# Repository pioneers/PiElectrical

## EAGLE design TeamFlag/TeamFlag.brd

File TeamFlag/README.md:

#Team Flag

The Flag for the Robot, display California Gold or Yale Blue

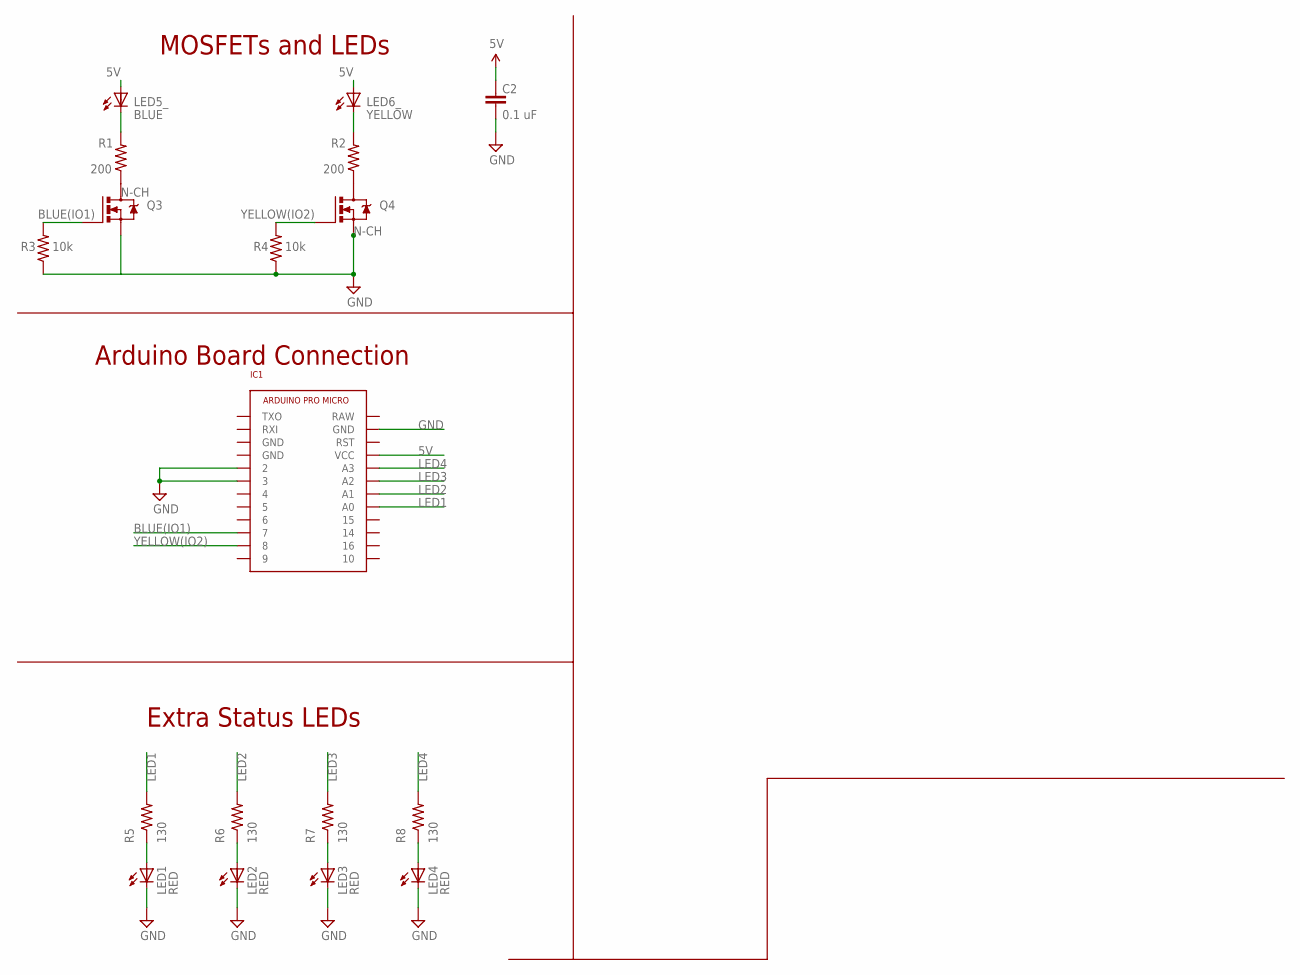
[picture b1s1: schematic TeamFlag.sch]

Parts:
C2: 0.1 uF; 0603-CAP
IC1: ARDUINO_PRO_MICROSMD; ARDUINO_PRO_MICRO_SM
LED1, LED2, LED3, LED4: RED; LED-0805
LED5_: BLUE; LED5MM-NOFLAT
LED6_: YELLOW; LED5MM-NOFLAT
Q3, Q4: N-CH; SOT23-3
R1, R2: 200; R0603
R3, R4: 10k; R0603
R5, R6, R7, R8: 130; R0603

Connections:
5V: C2.1, IC1.VCC, LED5_.A, LED6_.A
BLUE(IO1): IC1.7, Q3.1 (G), R3.2
BSOURCE: Q3.3 (D), R1.1
GND: C2.2, IC1.2, IC1.3, IC1.GND@2 (GND), LED1.C, LED2.C, LED3.C, LED4.C, Q3.2 (S), Q4.2 (S), R3.1, R4.1
LED1: IC1.A0, R5.2
LED1R: LED1.A, R5.1
LED2: IC1.A1, R6.2
LED2R: LED2.A, R6.1
LED3: IC1.A2, R7.2
LED3R: LED3.A, R7.1
LED4: IC1.A3, R8.2
LED4R: LED4.A, R8.1
unnamed: LED5_.K (C), R1.2
unnamed: LED6_.K (C), R2.2
YELLOW(IO2): IC1.8, Q4.1 (G), R4.2
YSOURCE: Q4.3 (D), R2.1

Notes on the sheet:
MOSFETs and LEDs
Extra Status LEDs
Arduino Board Connection

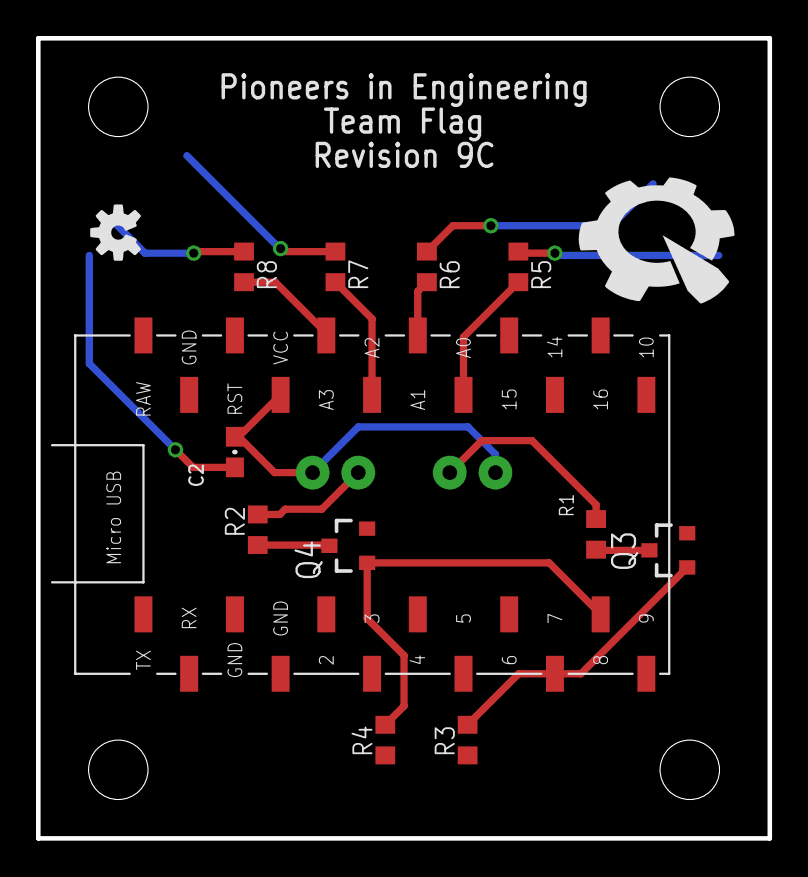
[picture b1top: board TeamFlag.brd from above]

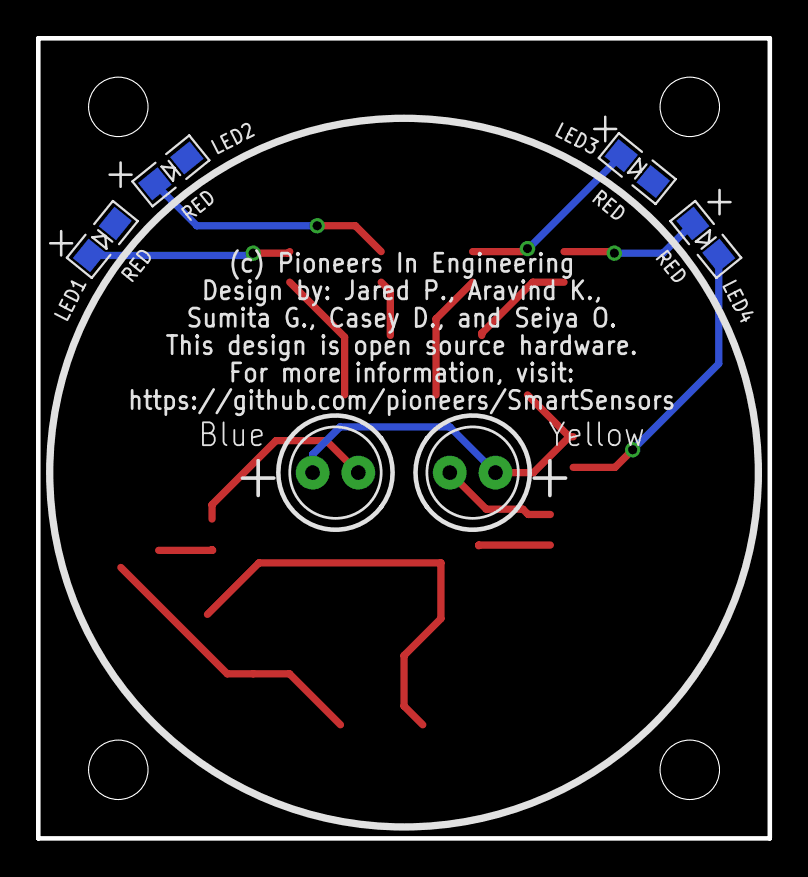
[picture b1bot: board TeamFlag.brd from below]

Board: 2 copper layers, 40.6 x 44.5 mm, 24 parts (6 on the bottom side), 16 nets.

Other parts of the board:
U$1: PIE-LOGO-SMALL
U$2: OSHW-LOGO-S
U$11, U$12, U$13, U$14: STAND-OFF

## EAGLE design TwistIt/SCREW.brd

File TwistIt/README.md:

#TwistIt

Screw terminal based potentiometer/line follower/limit switch ultimate board

Named TwistIt for the screw terminal (open to suggestions)

Digital in Pins are all labeled "Arduino" in the pinout diagram

Analog pins are labeled as such

Analog pins can be used as digital, NOT vice versa

[2 Pin](https://www.sparkfun.com/products/8432) [3 pin](https://www.sparkfun.com/products/8433)

##Reed switches

Basically when it is placed in a magnetic field, the switch closes.

There surface mounts and through hole variants, but generally they have the same working range

For more specs, please view the link below:

http://www.digikey.com/product-search/en/switches/magnetic-reed-switches/1114199

It can be bought from Digikey, Sparkfun, Aliexpress, Amazon.

[AliExpress](https://www.aliexpress.com/item/10pcs-KSK-1A-Reed-Switch-2x14mm-Green-Glass-Usually-Open-For-Sensors-100-Original/32424207994.html)

To test it, connect it in series with a resistor and take the input from the point between them.

A sample of a simple code is shown below:

```
int reed = 2;

int LED = 3;

void setup() {

Serial.begin(9600);

pinMode(reed,INPUT);

pinMode(LED,OUTPUT);

}

void loop() {

if(digitalRead(reed)==HIGH){

digitalWrite(LED, HIGH);

}

else digitalWrite(3, LOW);

}
```
where an LED is attached to pin 3.

Please contact Ren Lingfei for more information.

## Yogi Bear Break Out

VNH2SP30 | APM
-------- | ---
5V | Vcc
GND | GND
EN | 14
INA | 16
INB | 10
CS | 8
PMW | 9
- | -
Encoder A | 2
Encoder B | 3
- | -
Red | 4
Yellow | 5
Green  6

[New Motor 1](https://e-smotor.en.alibaba.com/product/60220884310-801307434/37GB_spur_gear_motor_with_encoder.html?spm=a2700.7803228.1998738836.575.wFZGi0)

[New Motor 2](https://jslmotor.en.alibaba.com/product/60311538644-211952029/12v_24v_Pure_Metal_JGB37_3530B_Permanent_Magnet_High_Torque_24_Volt_Dc_Motor.html?spm=a2700.7803228.1998738836.185.6lh84F)

[Hardware Interrupts](https://www.arduino.cc/en/Reference/AttachInterrupt)

Encoder is all digital. A and B Out need to be pulled up and needs to be mapped to interrupt pins

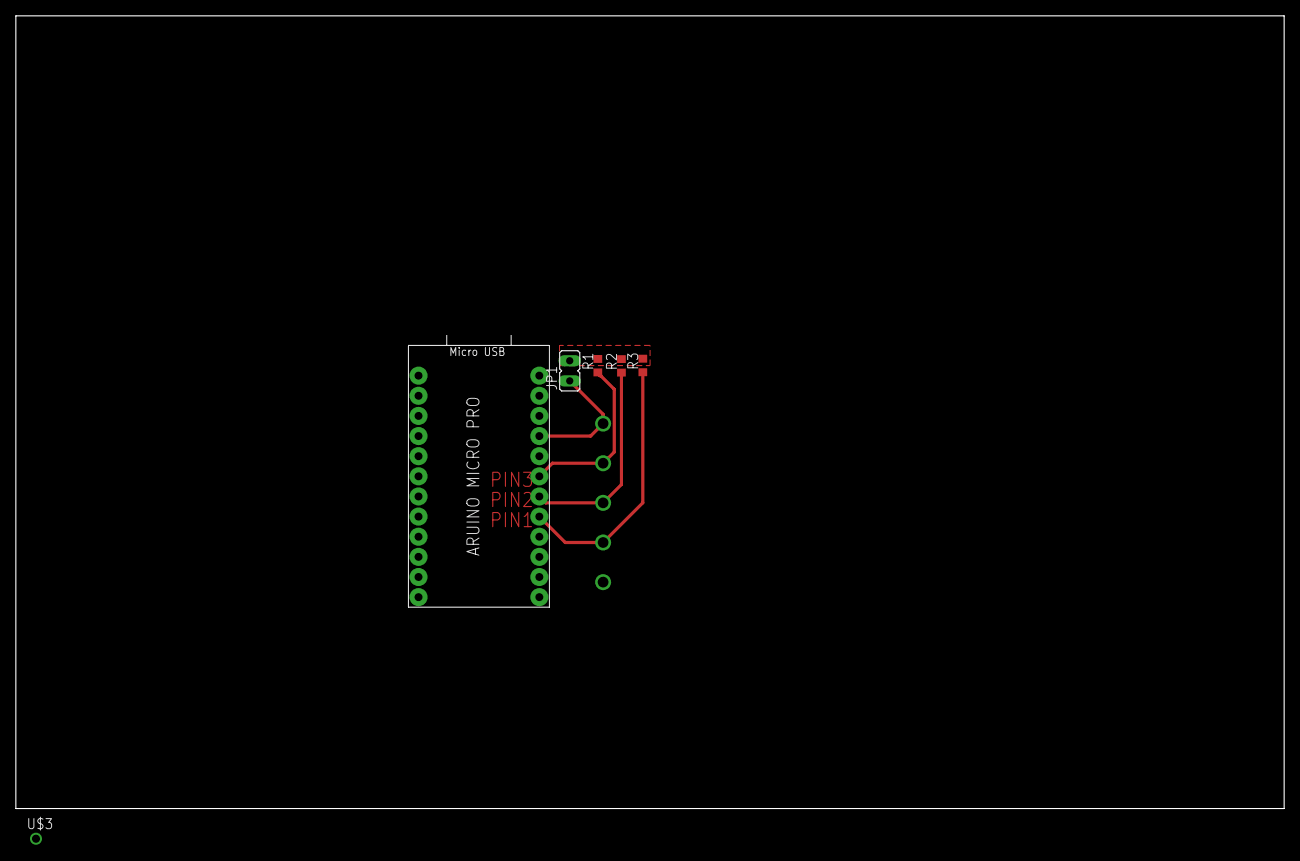
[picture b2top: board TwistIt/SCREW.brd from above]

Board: 2 copper layers, 160.0 x 100.0 mm, 7 parts (1 on the bottom side), 6 nets.

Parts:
JP1: JP1
R1, R2, R3: R0603
U$1: ARDUINO_PRO_MICRO
U$2: 5PIN_SCREW
U$3: POGO_PIN_394

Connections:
5V: JP1.2, R1.2, R2.2, R3.2
GND: U$1.GND@0, U$2.P$1
PIN1: R3.1, U$1.A0, U$2.P$2
PIN2: R2.1, U$1.A1, U$2.P$3
PIN3: R1.1, U$1.A2, U$2.P$4
VCC: JP1.1, U$1.VCC, U$2.P$5

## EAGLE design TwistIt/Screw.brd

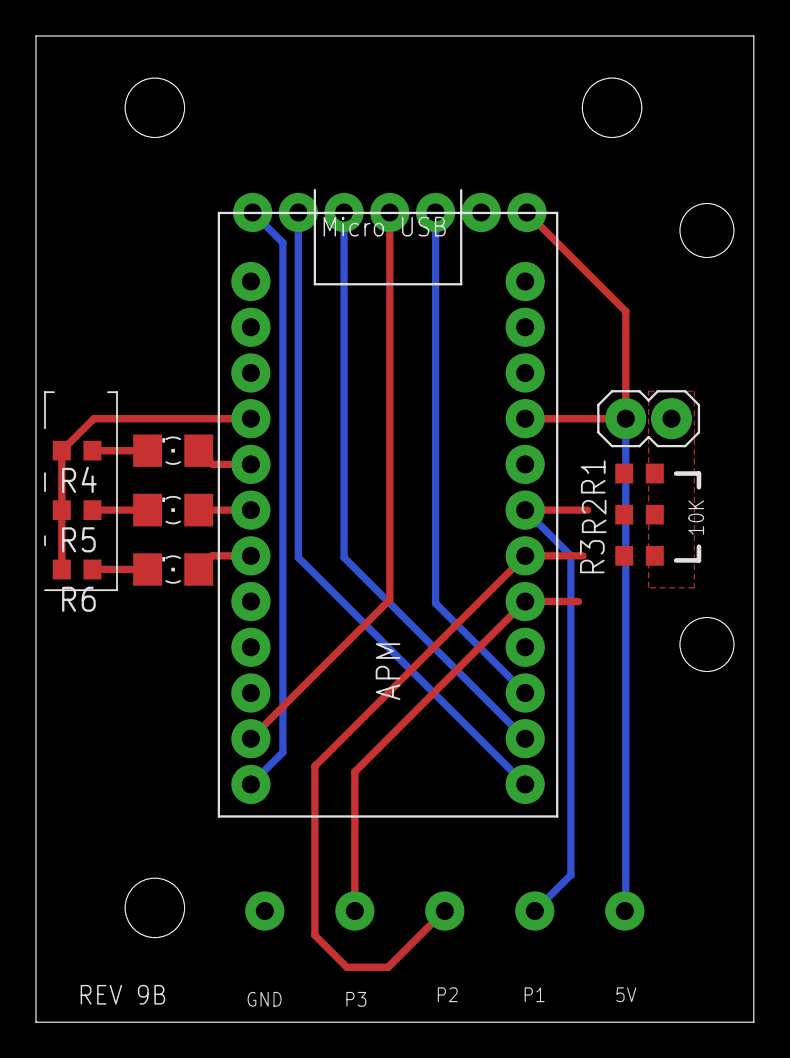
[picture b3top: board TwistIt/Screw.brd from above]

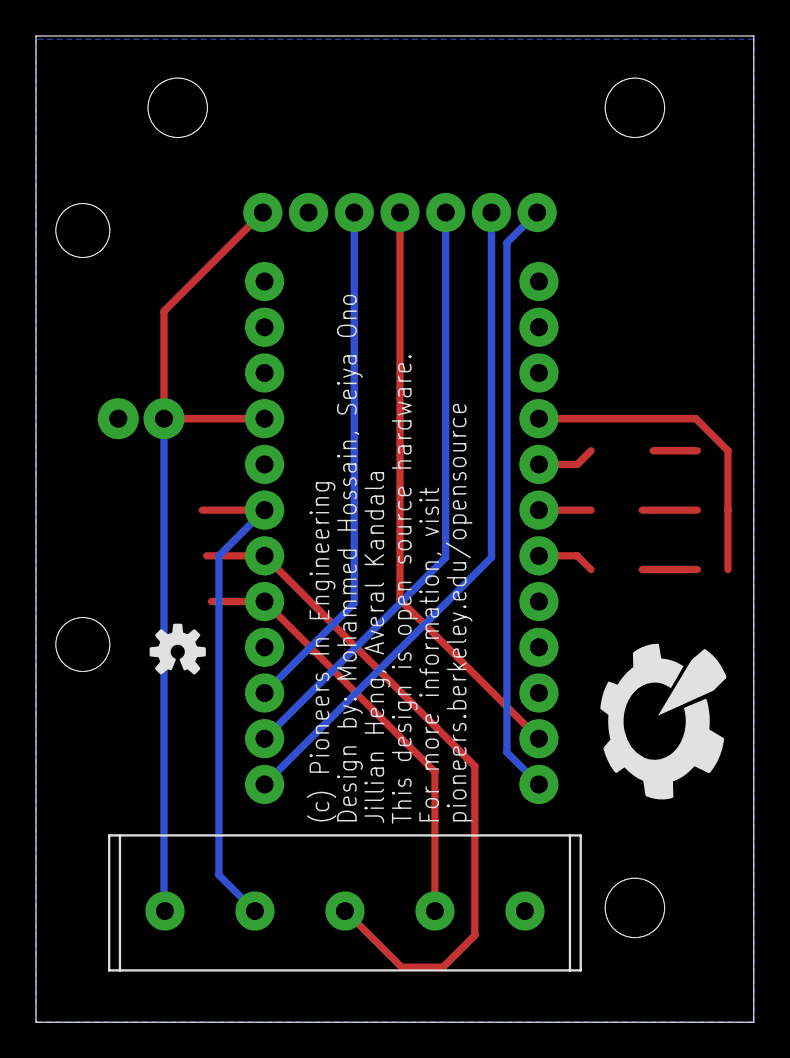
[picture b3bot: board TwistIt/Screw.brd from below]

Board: 2 copper layers, 39.9 x 54.8 mm, 18 parts (4 on the bottom side), 17 nets.

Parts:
5V_JUMPER: JUMPER
APM: ARDUINO_PRO_MICRO
BR1: VNH2SP30_MOTOR_CONTROLLER
LED1: RED; FKIT-LED-1206
LED2: YELLOW; FKIT-LED-1206
LED3: GREEN; FKIT-LED-1206
R1, R2, R3: 10K; R0603
R4, R5, R6: 330; R0603
ST1: 5PIN_SCREW
U$1, U$5, U$6: STAND-OFF
U$3: PIE-LOGO-SMALL
U$4: OSHW-LOGO-S

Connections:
5V: 5V_JUMPER.P$2, R1.2, R2.2, R3.2
CS: APM.8, BR1.CS
EN: APM.14, BR1.EN
GND: APM.GND@0, APM.GND@1, APM.GND@2, BR1.GND, R4.2, R5.2, R6.2, ST1.P$5
INA: APM.16, BR1.INA
INB: APM.10, BR1.INB
LED1: APM.2, LED1.A
LED2: APM.3, LED2.A
LED3: APM.4, LED3.A
unnamed: LED1.C, R4.1
unnamed: LED2.C, R5.1
unnamed: LED3.C, R6.1
P1: APM.A2, R1.1, ST1.P$2
P2: APM.A1, ST1.P$3
P3: APM.A0, R3.1, ST1.P$4
PWM: APM.9, BR1.PMW
VCC: 5V_JUMPER.P$1, APM.VCC, BR1.+5V, ST1.P$1

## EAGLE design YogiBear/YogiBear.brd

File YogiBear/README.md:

#YOGI BEAR

Yogi Bear is a cool bear.

[VNH2SP30](https://www.aliexpress.com/item/Free-shipping-VNH2SP30-in-stock/32235666194.html?spm=2114.01010208.3.154.pCpm6w&ws_ab_test=searchweb0_0,searchweb201602_4_10056_10065_10055_10068_10067_10054_10069_10059_418_10073_10017_10070_10060_10061_10052_10062_10053_10050_10051,searchweb201603_3&btsid=7e6b3cdb-1352-4e9c-9080-e427ead57444)

[MOSFET DIGI REEL] (http://www.digikey.com/product-detail/en/infineon-technologies/IPD90N03S4L-02/IPD90N03S4L-02DKR-ND/2231371)

[MOSFET CUT TAPE] (http://www.digikey.com/product-detail/en/infineon-technologies/IPD90N03S4L-02/IPD90N03S4L-02CT-ND/2231143)

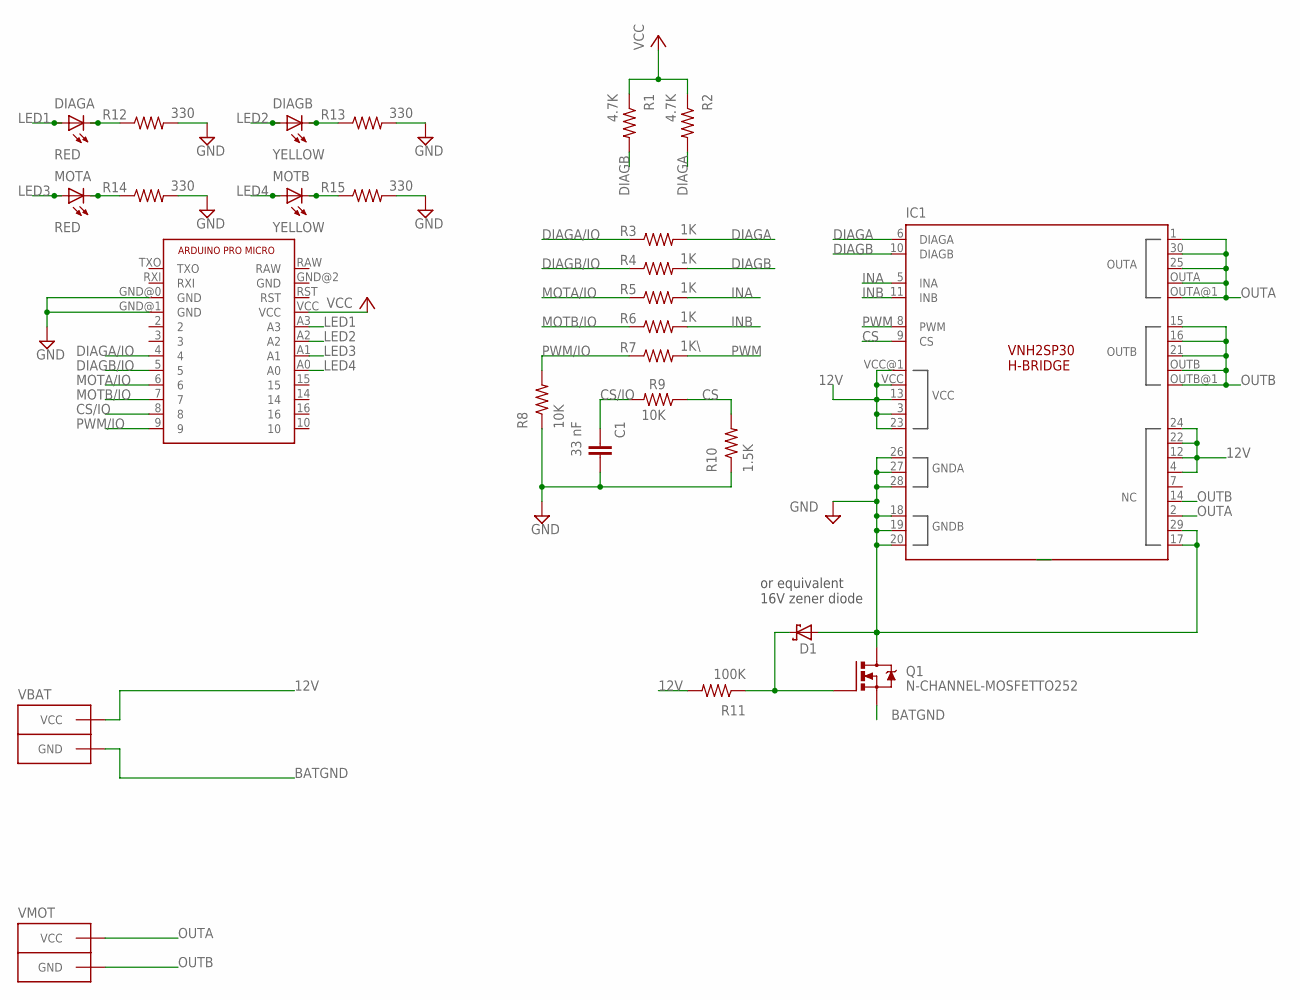
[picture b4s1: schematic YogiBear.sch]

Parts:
C1: 33 nF; 0603-CAP
D1: SCHOTTKY-DIODESMC; SMC
DIAGA: RED; LED-0603
DIAGB: YELLOW; LED-0603
IC1: VNH2SP30
MOTA: RED; LED-0603
MOTB: YELLOW; LED-0603
Q1: N-CHANNEL-MOSFETTO252; TO252
R1, R2: 4.7K; R0603
R3, R4, R5, R6: 1K; R0603
R7: 1K\; R0603
R8, R9: 10K; R0603
R10: 1.5K; R0603
R11: 100K; R0603
R12, R13, R14, R15: 330; R0603
U$1: ARDUINO_PRO_MICRO
VBAT: ANDERSONVERTICAL; ANDERSON_VERTICAL
VMOT: ANDERSONVERTICAL; ANDERSON_VERTICAL

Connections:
12V: IC1.3 (VCC), IC1.4 (NC5), IC1.12 (NC6), IC1.13 (VCC), IC1.22 (NC7), IC1.23 (VCC), IC1.24 (NC8), IC1.VCC, IC1.VCC@1 (VCC), R11.2, VBAT.PIN2 (VCC)
BATGND: Q1.2 (S), VBAT.PIN1 (GND)
CS: IC1.9 (CS), R9.1, R10.2
CS/IO: C1.1, R9.2, U$1.8
DIAGA: IC1.6 (DIAGA), R2.2, R3.2
DIAGA/IO: R3.1, U$1.4
DIAGB: IC1.10 (DIAGB), R1.2, R4.2
DIAGB/IO: R4.1, U$1.5
GND: C1.2, D1.A, IC1.17 (NC), IC1.18 (GNDB), IC1.19 (GNDB), IC1.20 (GNDB), IC1.26 (GNDA), IC1.27 (GNDA), IC1.28 (GNDA), IC1.29 (NC1), Q1.3 (D), R8.1, R10.1, R12.2, R13.2, R14.2, R15.2, U$1.GND@0 (GND), U$1.GND@1 (GND)
INA: IC1.5 (INA), R5.2
INB: IC1.11 (INB), R6.2
LED1: DIAGA.A, U$1.A3
LED2: DIAGB.A, U$1.A2
LED3: MOTA.A, U$1.A1
LED4: MOTB.A, U$1.A0
MOTA/IO: R5.1, U$1.6
MOTB/IO: R6.1, U$1.7
unnamed: D1.C, Q1.1 (G), R11.1
unnamed: MOTB.C, R15.1
unnamed: MOTA.C, R14.1
unnamed: DIAGB.C, R13.1
unnamed: DIAGA.C, R12.1
NC4: IC1.7 (NC4)
OUTA: IC1.1 (OUTA), IC1.2 (NC2), IC1.25 (OUTA), IC1.30 (OUTA), IC1.OUTA, IC1.OUTA@1 (OUTA), VMOT.PIN2 (VCC)
OUTB: IC1.14 (NC3), IC1.15 (OUTB), IC1.16 (OUTB), IC1.21 (OUTB), IC1.OUTB, IC1.OUTB@1 (OUTB), VMOT.PIN1 (GND)
PWM: IC1.8 (PWM), R7.2
PWM/IO: R7.1, R8.2, U$1.9
VCC: R1.1, R2.1, U$1.VCC

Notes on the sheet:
or equivalent 16V zener diode

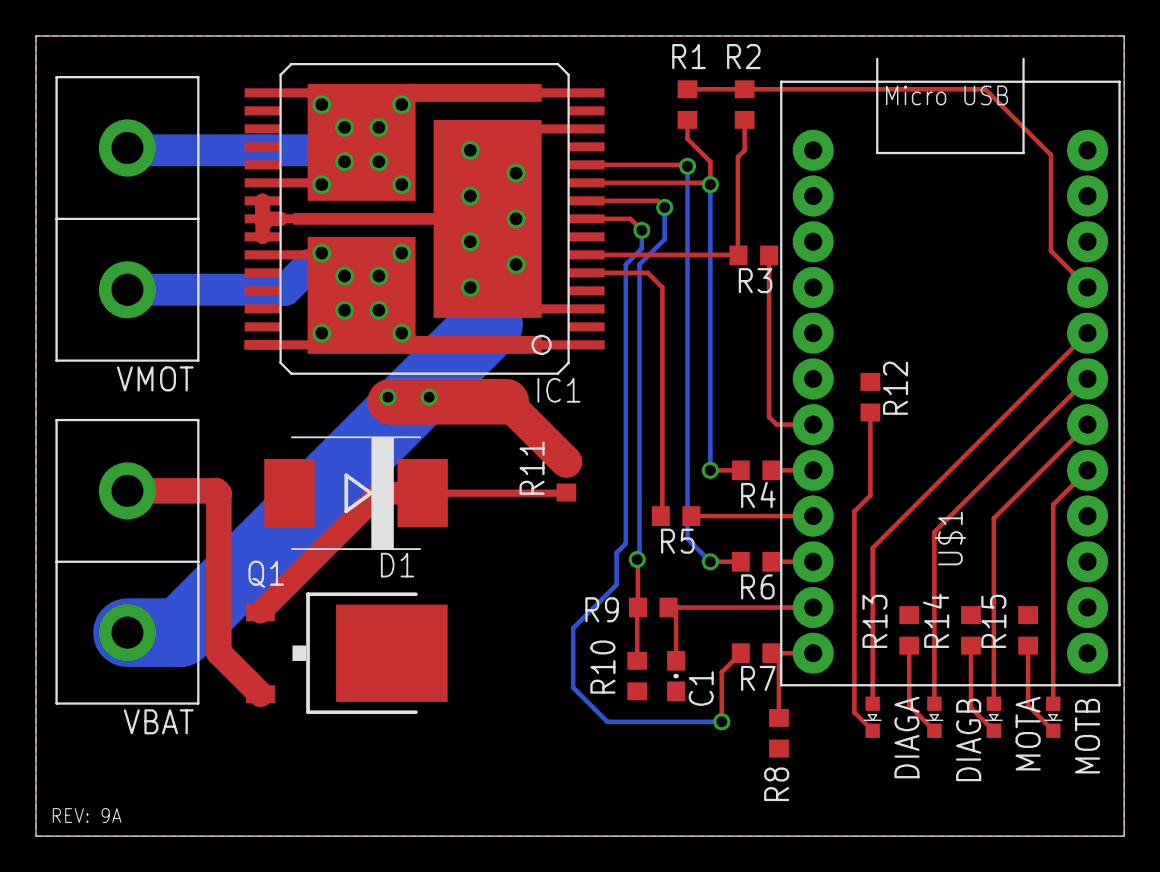
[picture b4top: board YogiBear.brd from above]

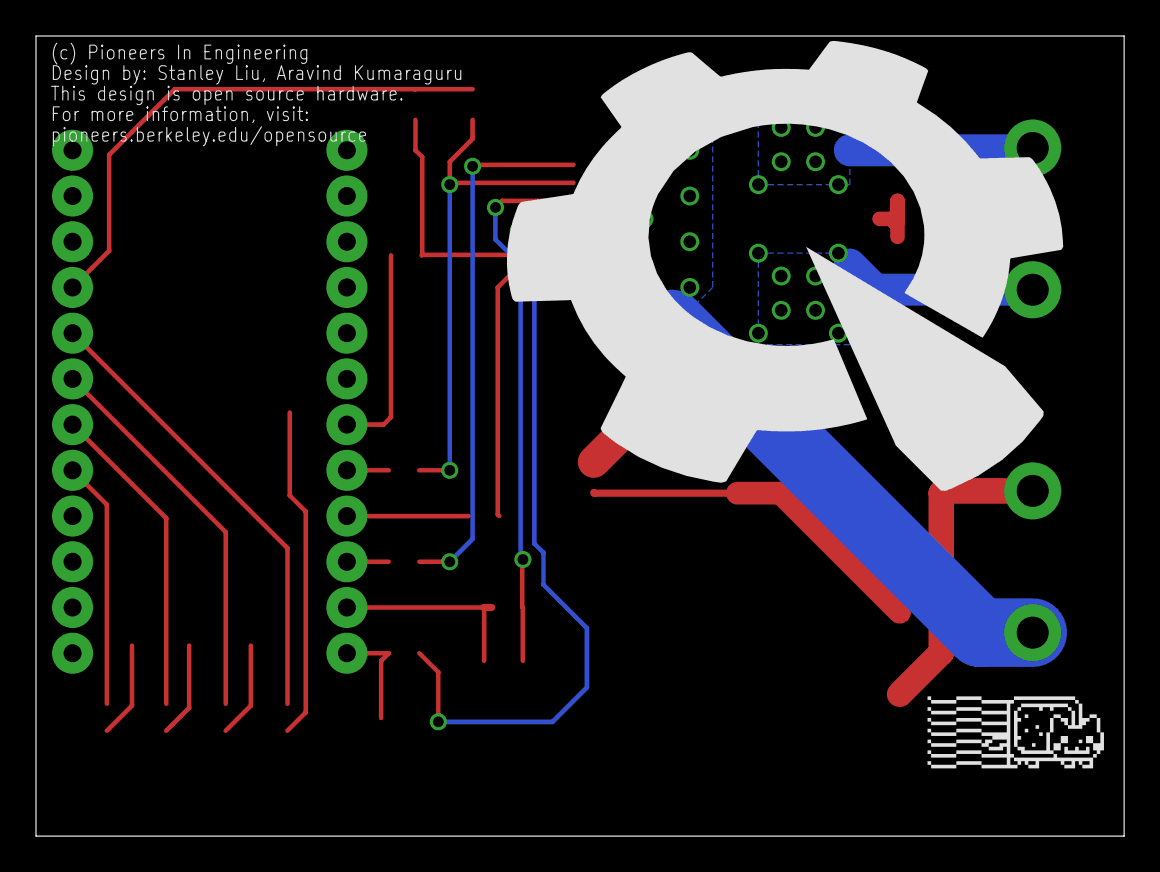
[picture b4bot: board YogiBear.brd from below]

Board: 2 copper layers, 60.5 x 44.5 mm, 28 parts (2 on the bottom side), 27 nets.

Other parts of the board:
U$2: PIE-LOGO
U$3: NYAN-1CM

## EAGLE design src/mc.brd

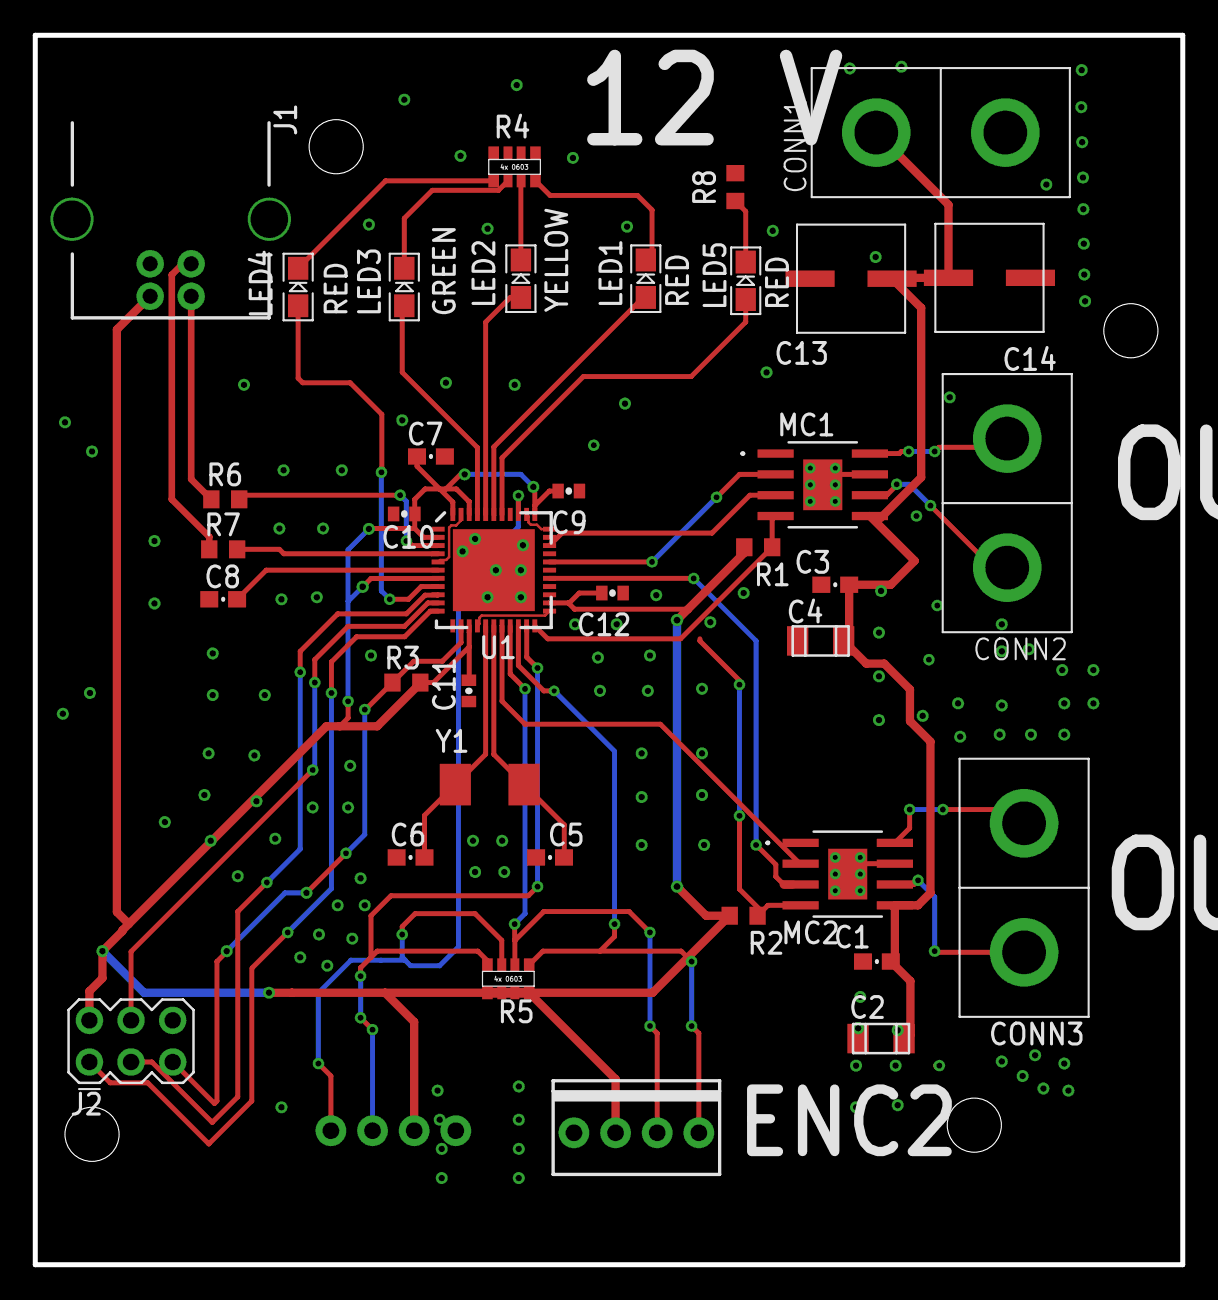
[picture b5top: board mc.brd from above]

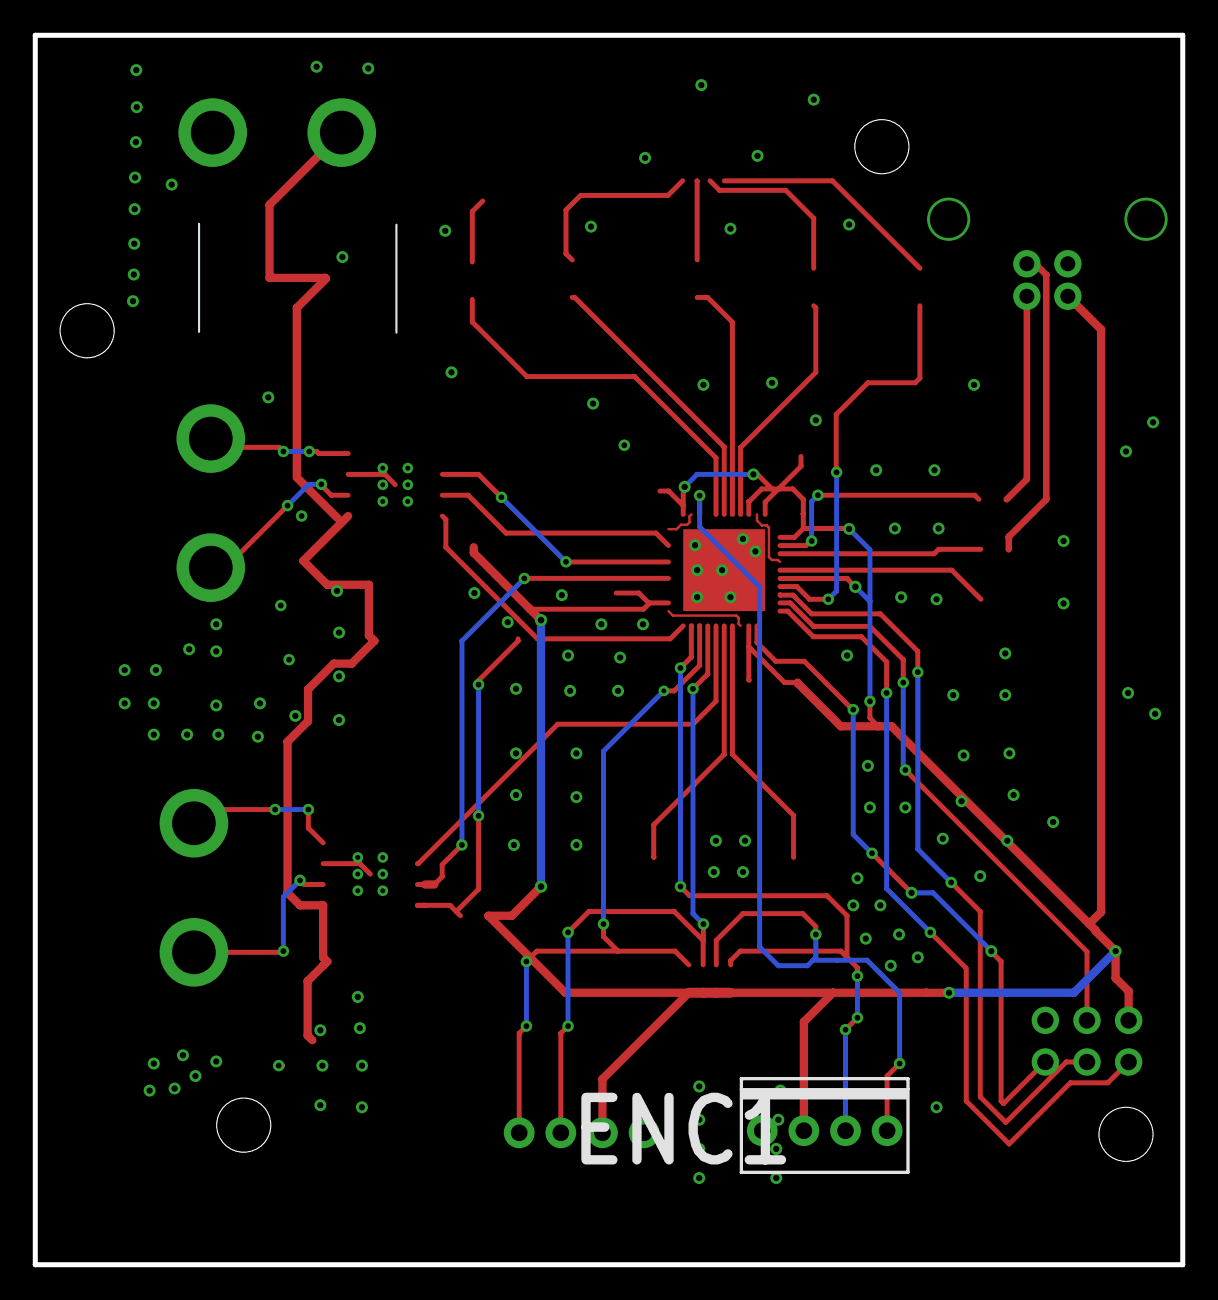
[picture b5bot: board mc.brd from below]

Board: 2 copper layers, 70.0 x 75.0 mm, 43 parts (2 on the bottom side), 37 nets.

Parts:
C1, C3: 0.1 µF; 0603-CAP
C2, C4: 47 µF; 1206
C5, C6: 18pF; 0603-CAP
C7: 1 uF; 0603-CAP
C8: 1uF; 0603-CAP
C9, C10, C11, C12: 0.1 uF; 0402-CAP
C13, C14: LELON_ELECTROLYTIC_CAP; LELON_CAP
CONN1, CONN2, CONN3: ANDERSONVERTICAL; ANDERSON_VERTICAL
ENC1, ENC2: 1X04-MTA
J1: USB_B_PTH; USB-B-PTH
J2: AVR_SPI_PRG_6MA03-2; MA03-2
LED1, LED4, LED5: RED; LED-0805
LED2: YELLOW; LED-0805
LED3: GREEN; LED-0805
MC1, MC2: DRV8872DDAR; DDA0008H_N_TEX
R1, R2, R3: 10k; R0603
R4: 330; 4X-0603
R5: 10k; 4X-0603
R6, R7: 22; R0603
R8: 330; R0603
U1: 32U4; QFN-44
U$1, U$2, U$3, U$4: STAND-OFF
U$5: PIE-LOGO
Y1: CRYSTAL-SMD-5.0X3.2-2PIN

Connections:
A1: ENC1.3, R5.4, U1.21
A2: ENC1.4, R5.3, U1.36
AIN1: MC1.3, U1.31
AIN2: MC1.2, U1.29
AOUT1: CONN2.PIN2, MC1.6
AOUT2: CONN2.PIN1, MC1.8
B1: ENC2.3, R5.2, U1.19
B2: ENC2.4, R5.1, U1.20
BIN1: MC2.3, U1.27
BIN2: MC2.2, U1.18
BOUT1: CONN3.PIN2, MC2.6
BOUT2: CONN3.PIN1, MC2.8
D+: J1.D+, R7.1
D-: J1.D-, R6.1
FAULT_N: MC1.4, MC2.4, R1.2, R2.2, U1.22
GND: C1.2, C2.2, C3.2, C4.2, C5.1, C6.1, C7.1, C8.1, C9.1, C10.1, C11.1, C12.1, C13.P$2, C14.P$2, CONN1.PIN1, ENC1.1, ENC2.1, J1.GND, J1.SHLD1, J1.SHLD2, J2.6, MC1.1, MC1.7, MC1.9, MC1.P$1, MC1.P$2, MC1.P$3, MC1.P$4, MC1.P$5, MC1.P$6, MC2.1, MC2.7, MC2.9, MC2.P$1, MC2.P$2, MC2.P$3, MC2.P$4, MC2.P$5, MC2.P$6, R4.1, R4.2, R4.3, R4.4, R8.2, U1.5, U1.15, U1.23, U1.33, U1.35, U1.43
HEARTBEAT: LED5.A, U1.38
LED1: LED1.A, U1.39
LED2: LED2.A, U1.40
LED3: LED3.A, U1.41
LR1: LED1.C, R4.8
LR2: LED2.C, R4.7
LR3: LED3.C, R4.6
LR4: LED4.C, R4.5
unnamed: C8.2, U1.6
unnamed: C5.2, U1.17, Y1.P$2
unnamed: R6.2, U1.3
unnamed: R7.2, U1.4
unnamed: LED5.C, R8.1
unnamed: C6.2, U1.16, Y1.P$1
RST: J2.5, R3.2, U1.13
RXLED: LED4.A, U1.8
SCLK: J2.3, U1.9
SDATI: J2.4, U1.10
SDATO: J2.1, U1.11
VCC: C7.2, C9.2, C10.2, C11.2, C12.2, ENC1.2, ENC2.2, J1.VBUS, J2.2, R1.1, R2.1, R3.1, R5.5, R5.6, R5.7, R5.8, U1.2, U1.7, U1.14, U1.24, U1.34, U1.42, U1.44
VM: C1.1, C2.1, C3.1, C4.1, C13.P$1, C14.P$1, CONN1.PIN2, MC1.5, MC2.5
